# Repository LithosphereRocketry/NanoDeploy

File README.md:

# NanoDeploy

## NOTE: This repository is archived. Further development will continue at https://codeberg.org/scrapbry/NanoDeploy

## Firmware

Firmware for NanoDeploy is located in the `firmware` directory. Most day-to-day
operations are handled by that folder's Makefile.

### Build environment setup

The setup process for TI's MSP430 toolchain is pretty miserable on modern Linux.
See firmware/install-notes.md for details.

### Uploading

Run `make run` to upload the code to an attached MSP430 development board.

### Debugging

Run `make gdb` to upload the code to the attached dev board and start a GDB
server session. From a separate terminal, then run `msp430-gdb`. (The included
.gdbinit file should take care of all the necessary setup.)

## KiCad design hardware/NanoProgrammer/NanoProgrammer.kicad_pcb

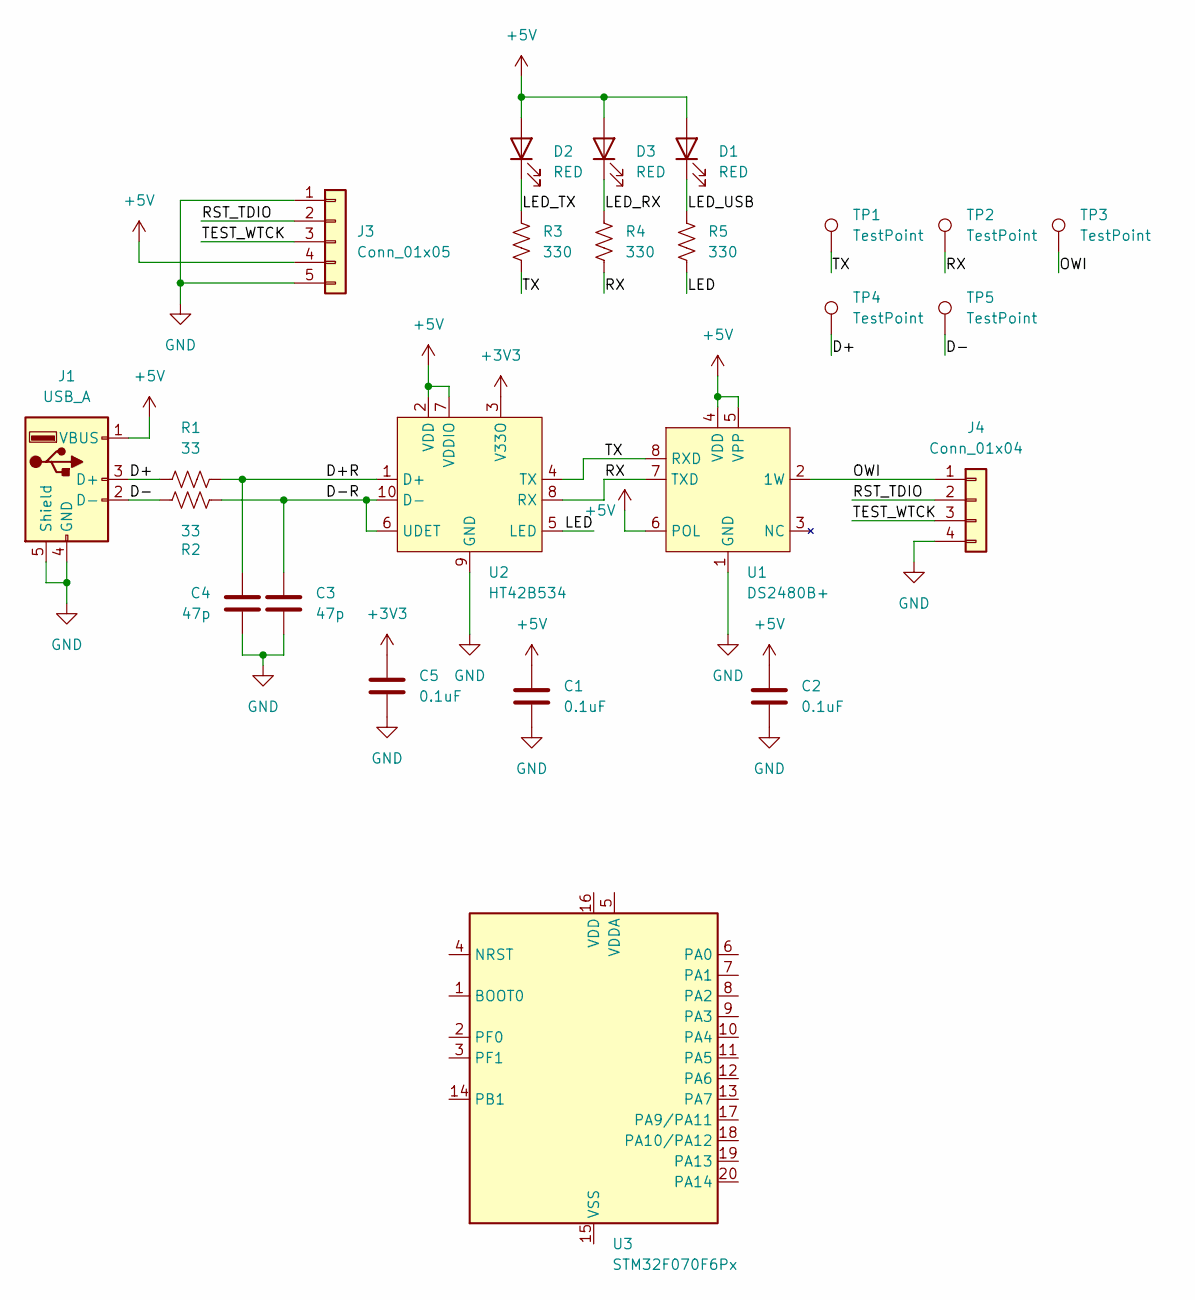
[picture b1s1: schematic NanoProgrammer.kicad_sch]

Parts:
C1, C2, C5: 0.1uF; C_0402_1005Metric; LCSC C1525
C3, C4: 47p; C_0402_1005Metric; LCSC C1567
D1, D2, D3: RED; LED_0603_1608Metric; LCSC C2286
J1: USB_A; USB_A_AdamTech_USB-AP-S-RA_Horizontal; JLCPCB_IGNORE ignore
J3: Conn_01x05; PinHeader_1x05_P2.54mm_Vertical; JLCPCB_IGNORE ignore
J4: Conn_01x04; Molex_PicoBlade_53047-0410_1x04_P1.25mm_Vertical; JLCPCB_IGNORE ignore
R1, R2: 33; R_0402_1005Metric; LCSC C25105
R3, R4, R5: 330; R_0402_1005Metric; LCSC C25104
TP1, TP2, TP3, TP4, TP5: TestPoint; TestPoint_THTPad_1.0x1.0mm_Drill0.5mm; JLCPCB_IGNORE ignore
U1: DS2480B+; SO-8_3.9x4.9mm_P1.27mm; LCSC C722462
U2: HT42B534; SSOP-10_3.9x4.9mm_P1.00mm; LCSC C493293
U3: STM32F070F6Px; TSSOP-20_4.4x6.5mm_P0.65mm

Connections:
+3V3: C5.1, U2.3 (V33O)
+5V: C1.1, C2.1, D1.2 (A), D2.2 (A), D3.2 (A), J1.1 (VBUS), J3.4, U1.4 (VDD), U1.5 (VPP), U1.6 (POL), U2.2 (VDD), U2.7 (VDDIO)
/D+: J1.3 (D+), R1.1, TP4.1
/D+R: C4.1, R1.2, U2.1 (D+)
/D-: J1.2 (D-), R2.1, TP5.1
/D-R: C3.1, R2.2, U2.6 (UDET), U2.10 (D-)
/LED: R5.1, U2.5 (LED)
/LED_RX: D3.1 (K), R4.2
/LED_TX: D2.1 (K), R3.2
/LED_USB: D1.1 (K), R5.2
/OWI: J4.1, TP3.1, U1.2 (1W)
/RST_TDIO: J3.2, J4.2
/RX: R4.1, TP2.1, U1.7 (TXD), U2.8 (RX)
/TEST_WTCK: J3.3, J4.3
/TX: R3.1, TP1.1, U1.8 (RXD), U2.4 (TX)
GND: C1.2, C2.2, C3.2, C4.2, C5.2, J1.4 (GND), J1.5 (Shield), J3.1, J3.5, J4.4, U1.1 (GND), U2.9 (GND)

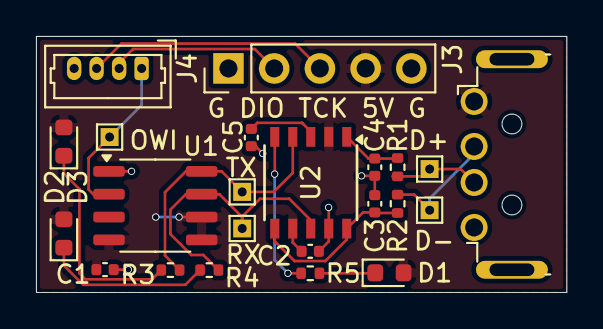
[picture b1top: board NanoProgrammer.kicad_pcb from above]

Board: 2 copper layers, 29.5 x 14.2 mm, 23 parts (0 on the bottom side), 16 nets.

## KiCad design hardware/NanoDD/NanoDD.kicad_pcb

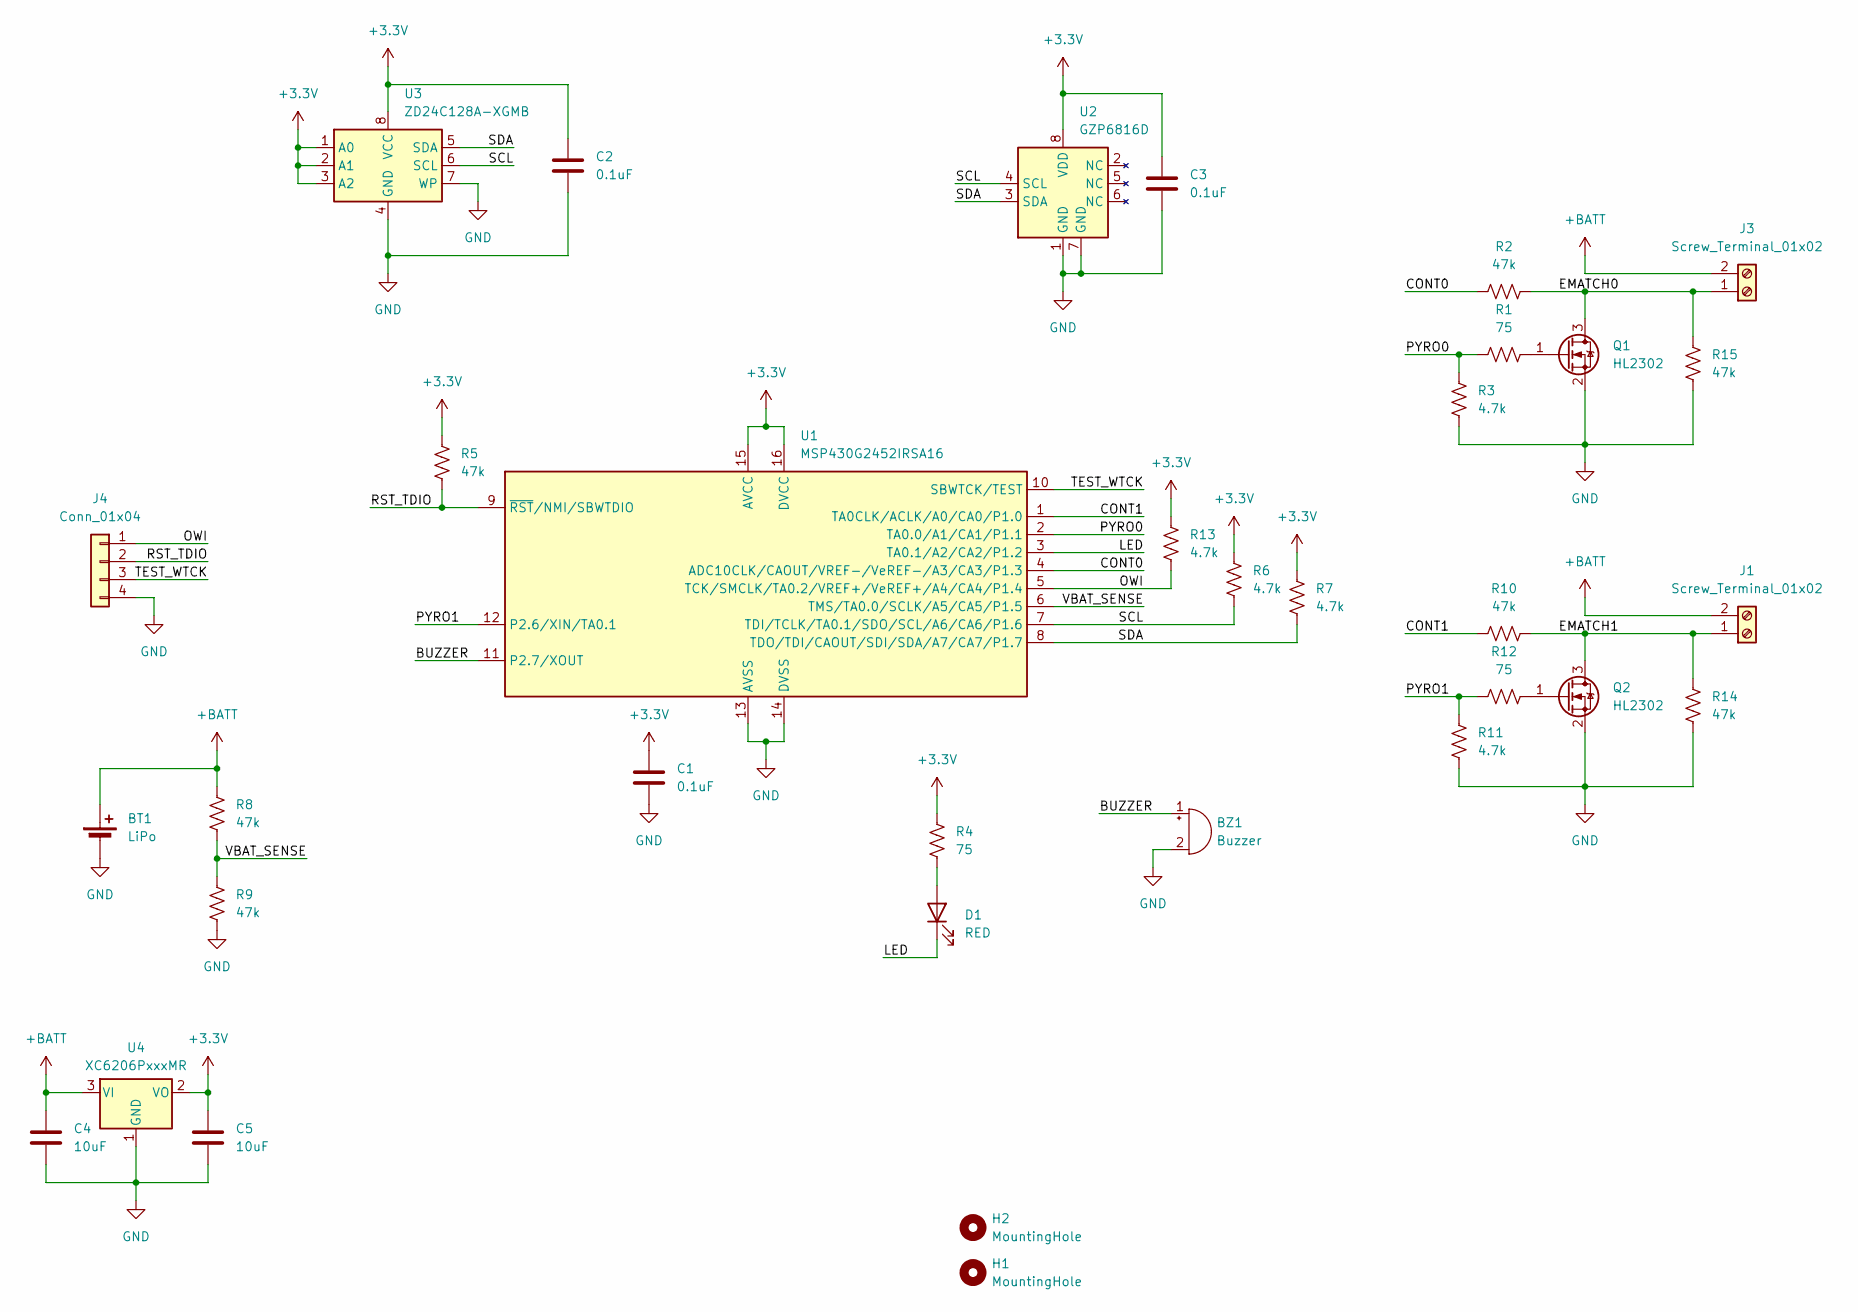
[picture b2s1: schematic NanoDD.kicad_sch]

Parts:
BT1: LiPo; PinHeader_1x02_P2.00mm_Vertical; JLCPCB_IGNORE ignore
BZ1: Buzzer; Buzzer_CUI_CPT-9019S-SMT; JLCPCB_IGNORE ignore
C1, C2, C3: 0.1uF; C_0402_1005Metric; LCSC C1525
C4, C5: 10uF; C_0603_1608Metric; LCSC C19702
D1: RED; LED_0603_1608Metric; LCSC C2286
H1, H2: MountingHole; MountingHole_2.2mm_M2; JLCPCB_IGNORE ignore
J1, J3: Screw_Terminal_01x02; TerminalBlock_TE_282834-2_1x02_P2.54mm_Horizontal; JLCPCB_IGNORE ignore
J4: Conn_01x04; Molex_PicoBlade_53047-0410_1x04_P1.25mm_Vertical; JLCPCB_IGNORE ignore
Q1, Q2: HL2302; SOT-23; LCSC C28646268
R1, R4, R12: 75; R_0402_1005Metric; LCSC C25133
R2, R5, R8, R9, R10, R14, R15: 47k; R_0402_1005Metric; LCSC C25792
R3, R6, R7, R11, R13: 4.7k; R_0402_1005Metric; LCSC C2906941
U1: MSP430G2452IRSA16; Texas_RSA_VQFN-16-1EP_4x4mm_P0.65mm_EP2.7x2.7mm; LCSC C74965
U2: GZP6816D; Bosch_LGA-8_2x2.5mm_P0.65mm_ClockwisePinNumbering; LCSC C3038127
U3: ZD24C128A-XGMB; TSSOP-8_4.4x3mm_P0.65mm; LCSC C918272
U4: XC6206PxxxMR; SOT-23-3; LCSC C5446

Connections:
+3.3V: C1.1, C2.1, C3.1, C5.1, R4.2, R5.1, R6.1, R7.1, R13.1, U1.15 (AVCC), U1.16 (DVCC), U2.8 (VDD), U3.1 (A0), U3.2 (A1), U3.3 (A2), U3.8 (VCC), U4.2 (VO)
+BATT: BT1.1 (+), C4.1, J1.2, J3.2, R8.1, U4.3 (VI)
/BUZZER: BZ1.1 (+), U1.11 (P2.7/XOUT)
/CONT0: R2.1, U1.4 (ADC10CLK/CAOUT/VREF-/VeREF-/A3/CA3/P1.3)
/CONT1: R10.1, U1.1 (TA0CLK/ACLK/A0/CA0/P1.0)
/EMATCH0: J3.1, Q1.3 (D), R2.2, R15.2
/EMATCH1: J1.1, Q2.3 (D), R10.2, R14.2
/LED: D1.1 (K), U1.3 (TA0.1/A2/CA2/P1.2)
/OWI: J4.1, R13.2, U1.5 (TCK/SMCLK/TA0.2/VREF+/VeREF+/A4/CA4/P1.4)
/PYRO0: R1.2, R3.1, U1.2 (TA0.0/A1/CA1/P1.1)
/PYRO1: R11.1, R12.2, U1.12 (P2.6/XIN/TA0.1)
/RST_TDIO: J4.2, R5.2, U1.9 (~RST/NMI/SBWTDIO)
/SCL: R6.2, U1.7 (TDI/TCLK/TA0.1/SDO/SCL/A6/CA6/P1.6), U2.4 (SCL), U3.6 (SCL)
/SDA: R7.2, U1.8 (TDO/TDI/CAOUT/SDI/SDA/A7/CA7/P1.7), U2.3 (SDA), U3.5 (SDA)
/TEST_WTCK: J4.3, U1.10 (SBWTCK/TEST)
/VBAT_SENSE: R8.2, R9.1, U1.6 (TMS/TA0.0/SCLK/A5/CA5/P1.5)
GND: BT1.2 (-), BZ1.2 (-), C1.2, C2.2, C3.2, C4.2, C5.2, J4.4, Q1.2 (S), Q2.2 (S), R3.2, R9.2, R11.2, R14.1, R15.1, U1.13 (AVSS), U1.14 (DVSS), U2.1 (GND), U2.7 (GND), U3.4 (GND), U3.7 (WP), U4.1 (GND)
unnamed: D1.2 (A), R4.1
unnamed: Q1.1 (G), R1.1
unnamed: Q2.1 (G), R12.1

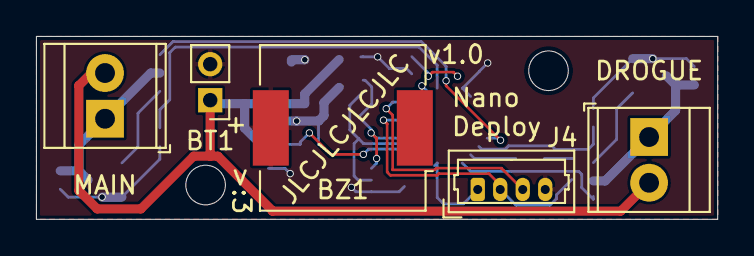
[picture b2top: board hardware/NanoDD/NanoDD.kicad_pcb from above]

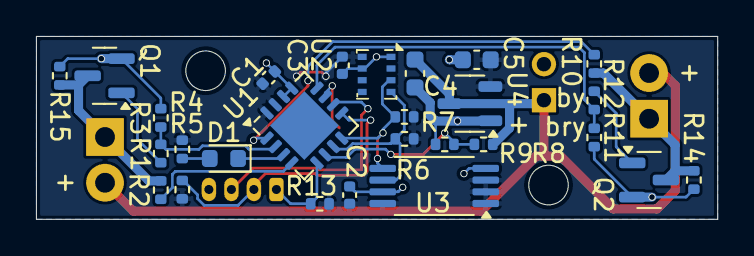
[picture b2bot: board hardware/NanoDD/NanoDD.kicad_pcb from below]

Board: 2 copper layers, 37.8 x 10.2 mm, 34 parts (27 on the bottom side), 20 nets.

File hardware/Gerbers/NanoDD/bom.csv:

Comment,Designator,Footprint,LCSC
AO3401A,"Q1,Q2",Package_TO_SOT_SMD:SOT-23,C15127
47k,"R2,R5,R8,R9,R10",Resistor_SMD:R_0402_1005Metric,C25792
MSP430G2452IRSA16,U1,Package_DFN_QFN:Texas_RSA_VQFN-16-1EP_4x4mm_P0.65mm_EP2.7x2.7mm,C74965
4.7k,"R3,R6,R7,R11",Resistor_SMD:R_0402_1005Metric,C2906941
0.1uF,"C1,C2,C3",Capacitor_SMD:C_0402_1005Metric,C1525
ZD24C128A-XGMB,U3,Package_SO:TSSOP-8_4.4x3mm_P0.65mm,C918272
270,"R1,R4,R12",Resistor_SMD:R_0402_1005Metric,C25155
MS5607-02BA,U5,Package_LGA:LGA-8_3x5mm_P1.25mm,C97627
XC6206PxxxMR,U4,Package_TO_SOT_SMD:SOT-23-3,C5446
RED,D1,LED_SMD:LED_0603_1608Metric,C2286
10uF,"C4,C5",Capacitor_SMD:C_0603_1608Metric,C19702

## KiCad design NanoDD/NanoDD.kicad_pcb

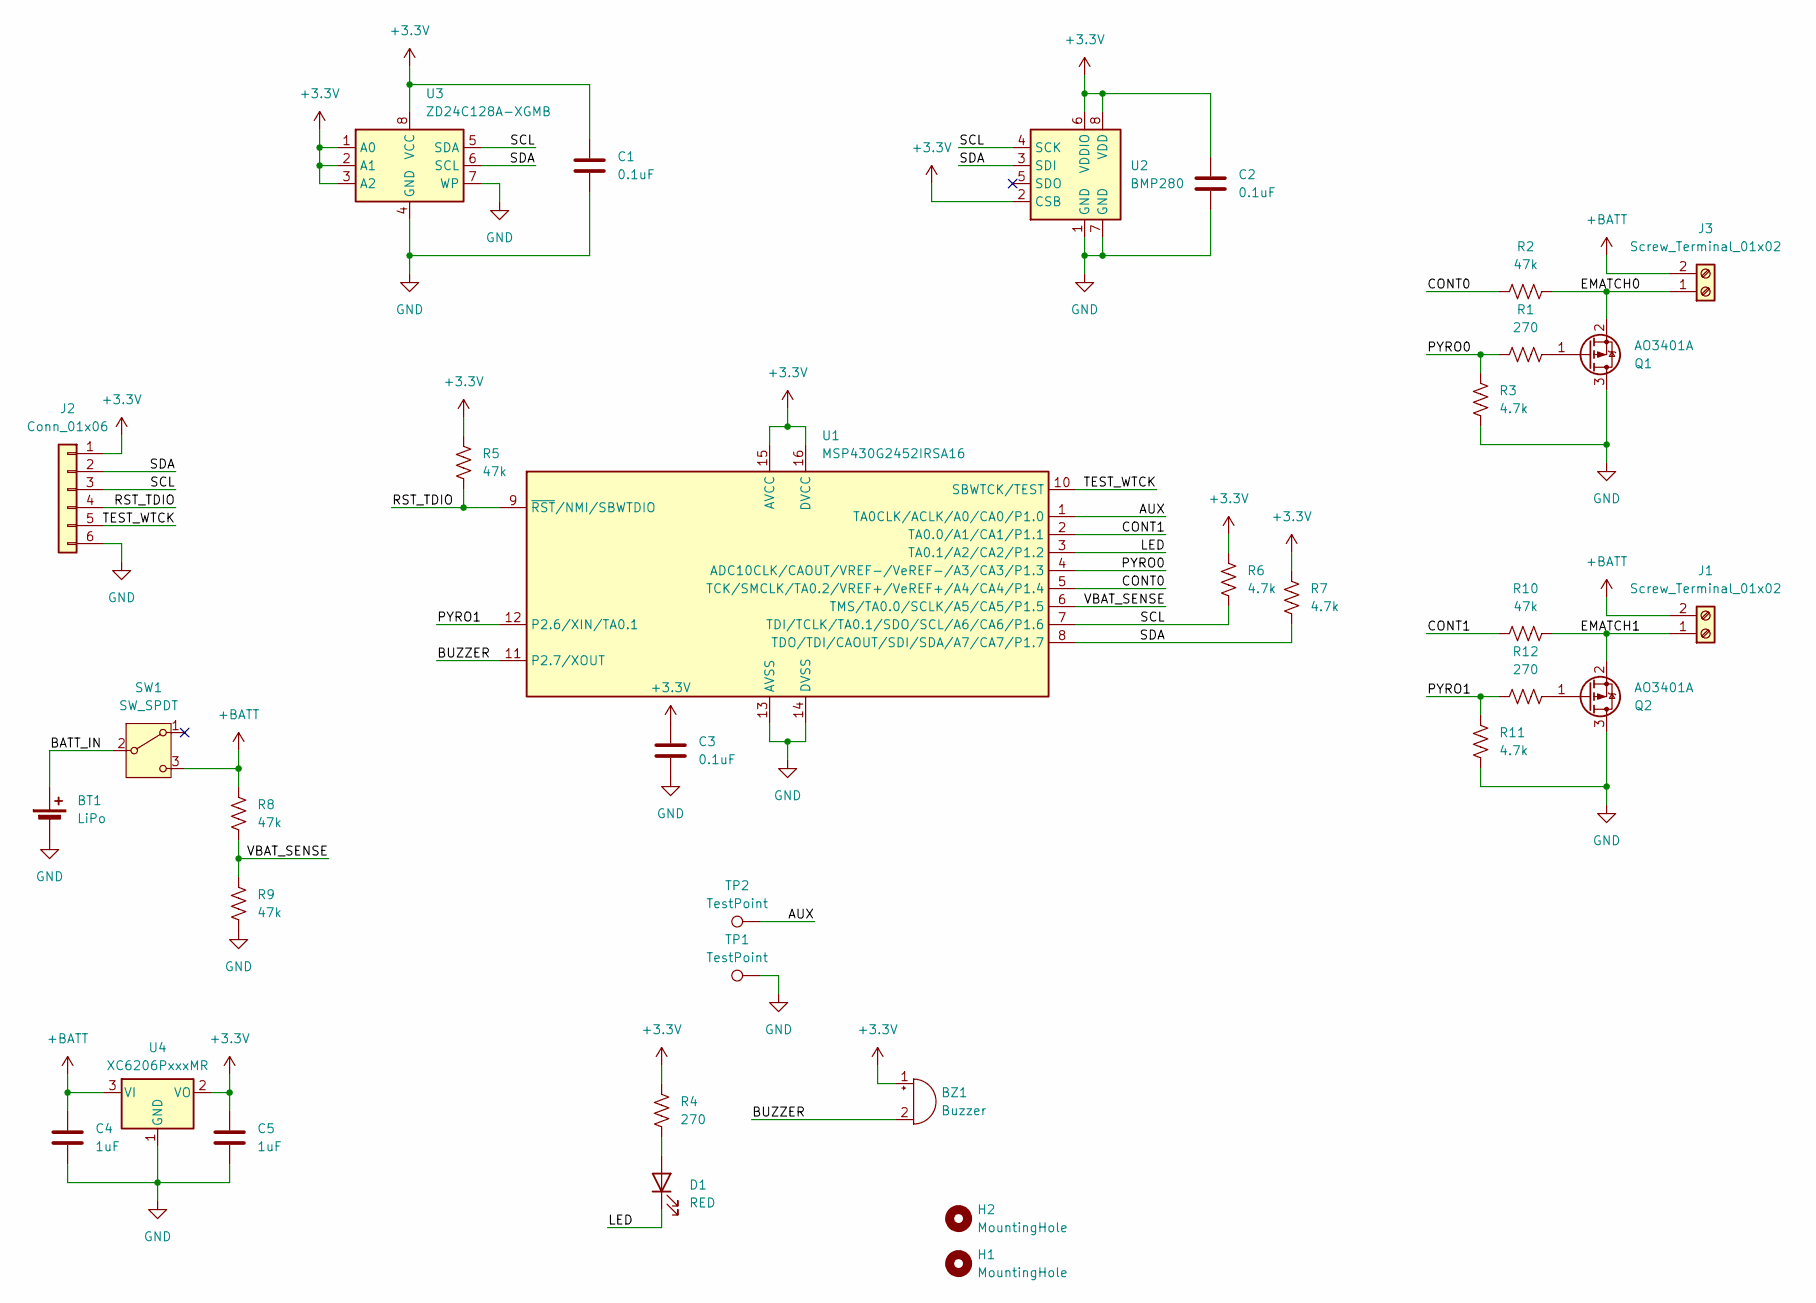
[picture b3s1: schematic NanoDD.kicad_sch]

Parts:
BT1: LiPo; PinHeader_1x02_P2.00mm_Vertical
BZ1: Buzzer; Buzzer_Mallory_AST1109MLTRQ
C1, C2, C3: 0.1uF; C_0402_1005Metric
C4, C5: 1uF; C_0603_1608Metric
D1: RED; LED_0603_1608Metric
H1, H2: MountingHole; MountingHole_2.2mm_M2
J1, J3: Screw_Terminal_01x02; TerminalBlock_TE_282834-2_1x02_P2.54mm_Horizontal
J2: Conn_01x06; Molex_PicoBlade_53047-0610_1x06_P1.25mm_Vertical
Q1, Q2: AO3401A; SOT-23
R1, R4, R12: 270; R_0402_1005Metric
R2, R5, R8, R10: 47k; R_0402_1005Metric
R3, R6, R7, R11: 4.7k; R_0402_1005Metric
R9: 47k; C_0402_1005Metric
SW1: SW_SPDT; MK-12C02-GXXX
TP1, TP2: TestPoint; TestPoint_Pad_1.5x1.5mm
U1: MSP430G2452IRSA16; Texas_RSA_VQFN-16-1EP_4x4mm_P0.65mm_EP2.7x2.7mm
U2: BMP280; Bosch_LGA-8_2x2.5mm_P0.65mm_ClockwisePinNumbering
U3: ZD24C128A-XGMB; TSSOP-8_4.4x3mm_P0.65mm
U4: XC6206PxxxMR; SOT-23-3

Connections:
+3.3V: BZ1.1 (+), C1.1, C2.1, C3.1, C5.1, J2.1, R4.2, R5.1, R6.1, R7.1, U1.15 (AVCC), U1.16 (DVCC), U2.2 (CSB), U2.6 (VDDIO), U2.8 (VDD), U3.1 (A0), U3.2 (A1), U3.3 (A2), U3.8 (VCC), U4.2 (VO)
+BATT: C4.1, J1.2, J3.2, R8.1, SW1.3 (C), U4.3 (VI)
/AUX: TP2.1, U1.1 (TA0CLK/ACLK/A0/CA0/P1.0)
/BATT_IN: BT1.1 (+), SW1.2 (B)
/BUZZER: BZ1.2 (-), U1.11 (P2.7/XOUT)
/CONT0: R2.1, U1.5 (TCK/SMCLK/TA0.2/VREF+/VeREF+/A4/CA4/P1.4)
/CONT1: R10.1, U1.2 (TA0.0/A1/CA1/P1.1)
/EMATCH0: J3.1, Q1.2 (S), R2.2
/EMATCH1: J1.1, Q2.2 (S), R10.2
/LED: D1.1 (K), U1.3 (TA0.1/A2/CA2/P1.2)
/PYRO0: R1.2, R3.1, U1.4 (ADC10CLK/CAOUT/VREF-/VeREF-/A3/CA3/P1.3)
/PYRO1: R11.1, R12.2, U1.12 (P2.6/XIN/TA0.1)
/RST_TDIO: J2.4, R5.2, U1.9 (~RST/NMI/SBWTDIO)
/SCL: J2.3, R6.2, U1.7 (TDI/TCLK/TA0.1/SDO/SCL/A6/CA6/P1.6), U2.4 (SCK), U3.5 (SDA)
/SDA: J2.2, R7.2, U1.8 (TDO/TDI/CAOUT/SDI/SDA/A7/CA7/P1.7), U2.3 (SDI), U3.6 (SCL)
/TEST_WTCK: J2.5, U1.10 (SBWTCK/TEST)
/VBAT_SENSE: R8.2, R9.1, U1.6 (TMS/TA0.0/SCLK/A5/CA5/P1.5)
GND: BT1.2 (-), C1.2, C2.2, C3.2, C4.2, C5.2, J2.6, Q1.3 (D), Q2.3 (D), R3.2, R9.2, R11.2, TP1.1, U1.13 (AVSS), U1.14 (DVSS), U2.1 (GND), U2.7 (GND), U3.4 (GND), U3.7 (WP), U4.1 (GND)
unnamed: D1.2 (A), R4.1
unnamed: Q1.1 (G), R1.1
unnamed: Q2.1 (G), R12.1

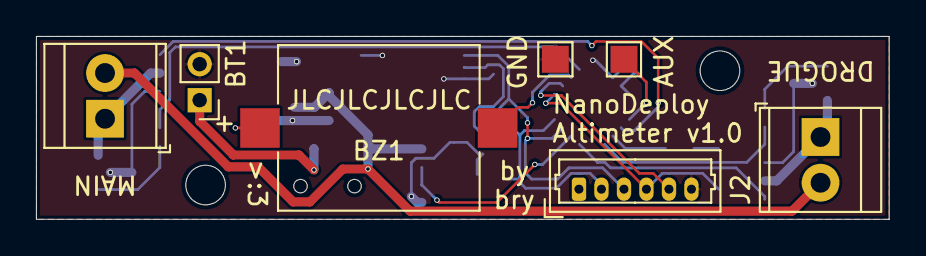
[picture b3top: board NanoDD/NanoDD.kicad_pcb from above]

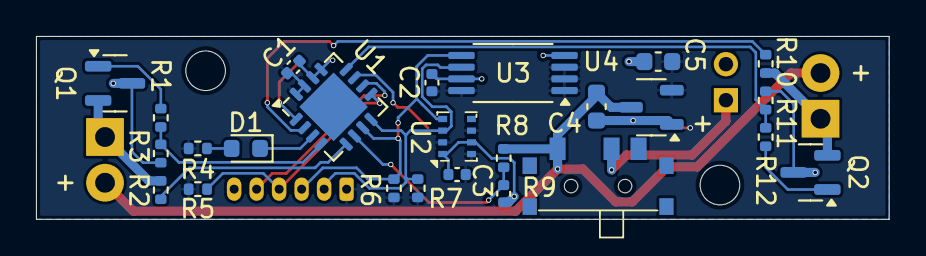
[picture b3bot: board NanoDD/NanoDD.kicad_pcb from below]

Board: 2 copper layers, 47.4 x 10.2 mm, 34 parts (25 on the bottom side), 21 nets.

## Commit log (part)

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2024-11-16 Initial PCB work
2024-11-16 Oops forgot to sleep and did all the layout
2024-11-16 Basic CCS project
2024-11-16 Deleted CCS files
2024-11-16 Untested blinky
2024-11-18 New PCB with makefile and MS5607
2024-11-18 Deleted excess generated files
2024-11-18 Removed extra copy of pcb
2024-11-20 Even more layout shrink, switch to barometer that's cheap on JLCPCB
2024-11-20 Name and version badge on PCB
2024-11-20 Fixed swapped SCL/SDA
2024-11-21 Correct MOSFETs and slightly better routing
2024-12-11 Ported to msp430-gcc because CCS on linux is bad
2024-12-11 Fixed flash test, the issue was that I'm dumb
2024-12-12 Got timers working
2024-12-12 Switched to TI distribution of GCC, fixed issue with non-static inline, import i2c library
2024-12-12 First data from GZP6816D
2024-12-24 Programmer board, also a lot of stuff that wasn't committed oops
2024-12-24 Support for pyro outputs, and start of baro calcs
2025-01-06 Altitude readings from sensor working
2025-01-08 EEPROM code, minor optimizations to baro code, updated I2C
2025-01-08 Reverted some build setting changes
2025-01-11 Read the first byte from OWI!
2025-01-19 moved OWI bridge code, and ENUMERATION WORKING
2025-01-19 Reading values over onewire, mostly
2025-02-02 Made make_divider importable
2025-02-02 Fixed the onewire timeouts, I think
2025-02-26 Kalman and a bunch of other mess
2025-10-05 Write up setup instructions
2025-10-17 huge bunch of uncommitted stuff idk what this is
2026-04-24 Work on analog, not done
2026-04-25 Unknown command warning
